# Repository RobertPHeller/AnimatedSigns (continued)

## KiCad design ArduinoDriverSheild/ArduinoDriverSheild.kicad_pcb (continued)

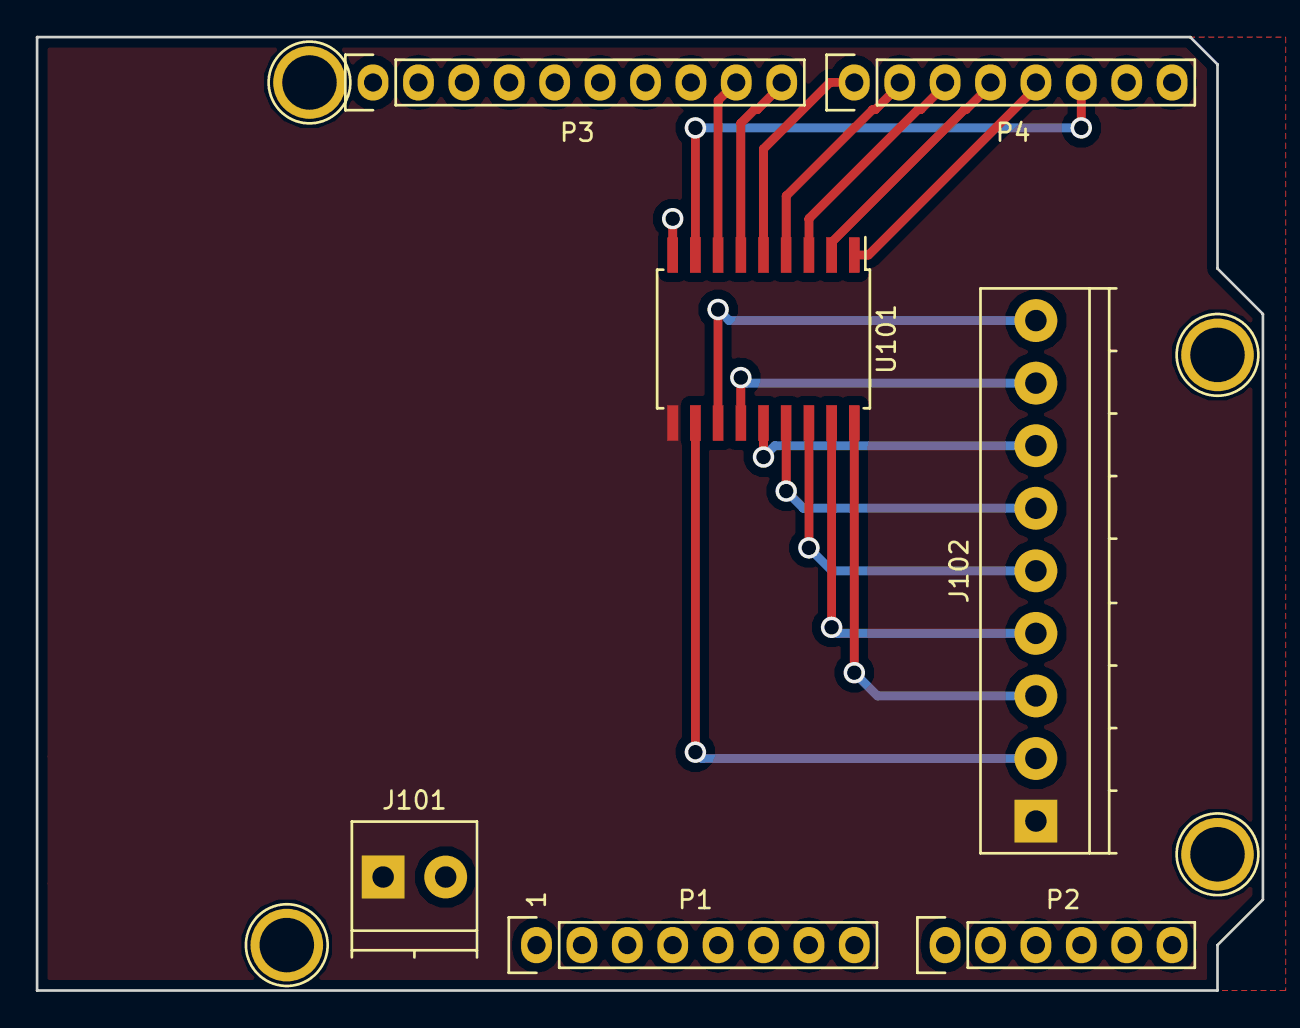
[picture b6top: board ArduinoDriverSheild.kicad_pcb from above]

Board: 2 copper layers, 68.6 x 53.3 mm, 11 parts (0 on the bottom side), 20 nets.

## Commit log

2023-02-03 Add .gitignore.
2023-02-04 Started on 8-ball Club Sign.
2023-02-04 Completed 8-ball club sign.
2023-02-04 Started on Arduino Driver Sheild.
2023-02-04 Completed on Arduino Driver Sheild.
2023-02-15 Final updates to 8 Ball Club sign.
2023-02-16 Single PCB version (thinner sign).
2023-02-17 GoodfellowsHall as 8 Ball Club, 6 foot lamp fixture.
2023-02-18 Updates to 8ballclubfloorLayout.
2023-02-19 Add Bar Overhead lights.
2023-02-19 Add Booth lights.
2023-03-08 Add MovieTheaterMarque.
2023-07-08 Upgrade Kicad version.
2023-07-28 Start firmware for STM32cubef303.
2023-07-28 Complete basic I/O and PWM mapping.
2023-07-29 Update git ignore.
2023-07-29 Complete firmware.
2023-08-26 Correct IRQ handler, reduce memory usage.
2023-08-27 Move all data to static RAM, adjust classes to be as memory compact as possible.
2023-08-28 Rename firmware to be more inclusive (multiple possible target MCUs).
2023-08-28 Add f767zi support.
2023-08-28 Add Hardware.hxx and HardwareDEFS.hxx, remove hardware.hxx from stm32f767zi target and map to even numbered pins (mapping to Mega Shield).
2023-08-28 Start mega shield.
2023-08-29 Complete shield for f767zi.
2023-08-29 F767-nucleo port completed.
2023-08-29 Remove L452 target.
2023-08-30 Minor update (GPIO ordering matching breadboard).
2023-08-30 Update F767 breadboard.
2023-09-04 Add psfile-0.9 (modified for python3)
2023-09-04 Remove psfile-0.9, start using PyX.
2023-09-05 Complete PostScript file generation.
2023-09-05 Add STL Export for 3D printed case.
2023-09-13 Update Makefile: current targets.
2023-09-14 Debugged Octal Driver for F767 board.
2023-11-03 Convert Step class to use a StateFlowTimer.
2023-11-04 Refactor Sequence and Step to use a StateFlow at the Sequence level.
2023-11-04 Fixup Event Identified calls.
2023-11-05 Add ESP32S3DevBoardDriver.
2023-11-05 Start on firmware.
2023-11-05 Completed firmware for ESP32S3DevBoardDriver.
2023-11-06 Color wires for easier assembly.
2023-11-07 First non-crashing version.
2023-11-07 Updated Esp32Ledc declration.
2023-11-07 Debugging the PWM driver...
2023-11-07 Revert to single timer and add get_duty() logging.
2023-11-09 Fix stop event.
2023-11-09 Add code to stop the output timer.
2023-11-09 Add code to stop the output timer and turn off outputs when stopping a sequence.
2023-11-09 Created kit booklet for 8ballsign.
2023-11-12 Create hood for lightbar.
2023-11-13 Completed kit booklets.
2023-12-05 First Draft of Bates Motel Light Board.
2023-12-06 Adjust silkscreen text.
2024-05-14 Completed Kit Booklet for Bates Motel sign.
2024-09-02 Finalize Bate's Motel.
